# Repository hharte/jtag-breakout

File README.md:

# JTAG Breakout Board

This is a simple breakout board for the standard 2x10 ARM JTAG header to a single row header.  Grounds are bussed and connected to the two mounting hole pads.

## Status
Board sent out for fabrication, not tested yet.

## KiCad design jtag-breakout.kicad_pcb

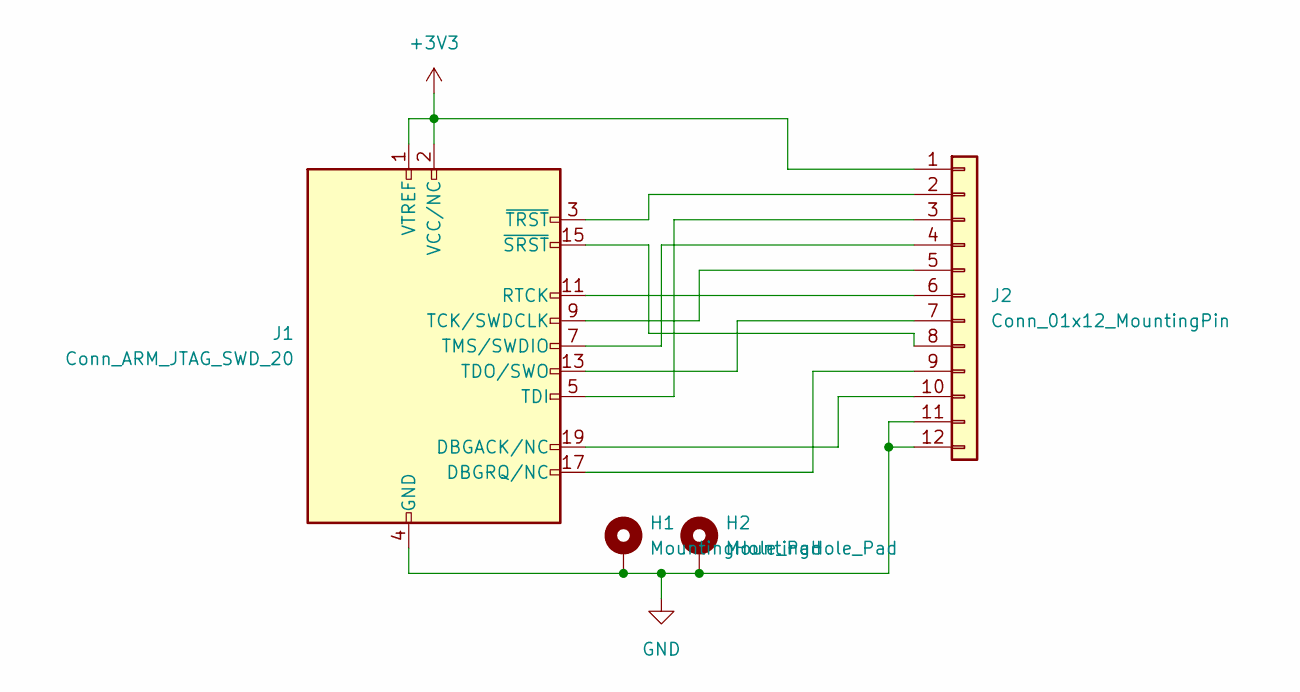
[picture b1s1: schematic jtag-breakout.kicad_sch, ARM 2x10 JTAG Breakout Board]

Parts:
H1, H2: MountingHole_Pad; MountingHole_3.7mm_Pad
J1: Conn_ARM_JTAG_SWD_20; IDC-Header_2x10_P2.54mm_Vertical
J2: Conn_01x12_MountingPin; PinHeader_1x12_P2.54mm_Horizontal

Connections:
+3V3: J1.1 (VTREF), J1.2 (VCC/NC), J2.1
GND: H1.1, H2.1, J1.4 (GND), J1.6 (GND), J1.8 (GND), J1.10 (GND), J1.12 (GND), J1.14 (GND), J1.16 (GND), J1.18 (GND), J1.20 (GND), J2.11, J2.12
unnamed: J1.19 (DBGACK/NC), J2.10
unnamed: J1.17 (DBGRQ/NC), J2.9
unnamed: J1.11 (RTCK), J2.6
unnamed: J1.9 (TCK/SWDCLK), J2.5
unnamed: J1.5 (TDI), J2.3
unnamed: J1.13 (TDO/SWO), J2.7
unnamed: J1.7 (TMS/SWDIO), J2.4
unnamed: J1.15 (~SRST), J2.8
unnamed: J1.3 (~TRST), J2.2

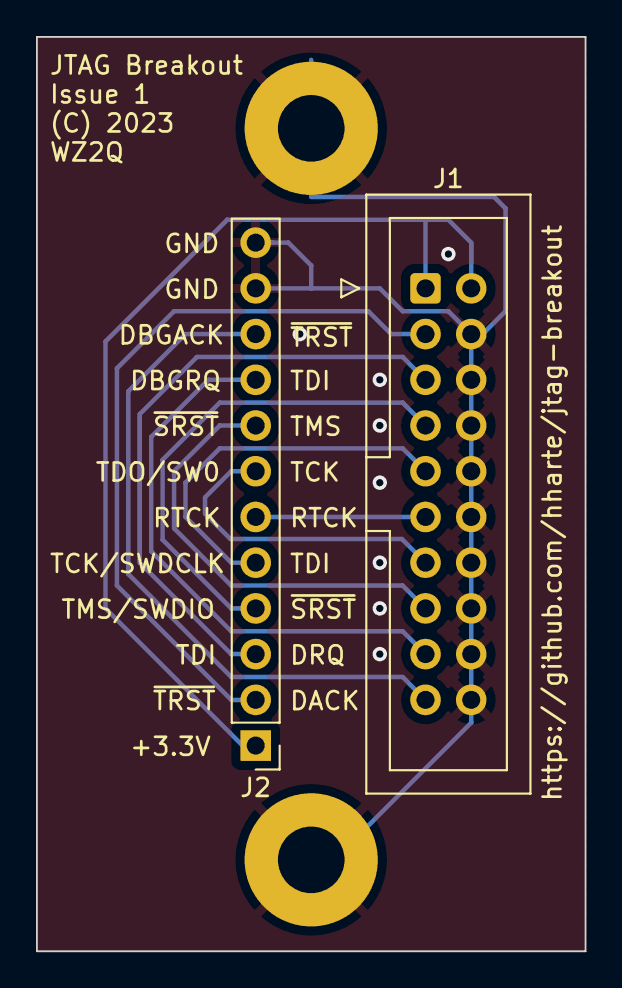
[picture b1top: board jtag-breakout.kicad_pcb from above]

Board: 2 copper layers, 30.5 x 50.8 mm, 4 parts (0 on the bottom side), 11 nets.

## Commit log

2023-10-02 Initial revision.
    Submitted to PCBWay.com for production.
2023-10-02 Add rendering of board.

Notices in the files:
jtag-breakout.kicad_pcb:
(C) 2023
